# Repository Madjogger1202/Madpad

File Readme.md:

# Madpad

> Custom macropad based on **RP2040** with display, audio feedback, and per-key RGB lighting.  
> Designed as a versatile input device for PC with extra features for interaction and visualization.  

---

## What’s on the board
- **RP2040 microcontroller**  
  - USB device (HID, MIDI, or custom protocols)  
- **IPS display (0.96")**  
  - Controller: **ST7735**  
  - For status output, macro layers, menus, or visual effects  
- **Microphone**: INMP441ACEZ-R7 (I²S interface)  
- **Piezo buzzer** with transistor driver for sound feedback  
- **Rotary encoder** with integrated push button  
- **8 mechanical keys** (macro switches)  
- **RGB lighting**:  
  - 1× WS2812 (1×1 mm) LED per key  
  - Additional WS2812 LEDs distributed across the board for **ambient light effects**  

---

## Connectivity
- **USB Type-C** for both power and PC connection  
- Enumerates as **USB HID keyboard/macropad** (firmware-dependent)  
- Can be extended to **MIDI control surface** or custom USB interfaces  

---

## Use Cases
- Macro pad for productivity (shortcuts, hotkeys, macros)  
- Custom controller for audio/video editing software  
- Mini MIDI controller for music applications  
- Experiment platform for RGB effects + input devices  

---

## Notes
- LED layout allows both **per-key lighting** and **global light animations**.  
- Buzzer and microphone make the board suitable for **interactive feedback** or audio experiments.  
- Rotary encoder + display add flexibility for menus, layers, or volume control.  

---

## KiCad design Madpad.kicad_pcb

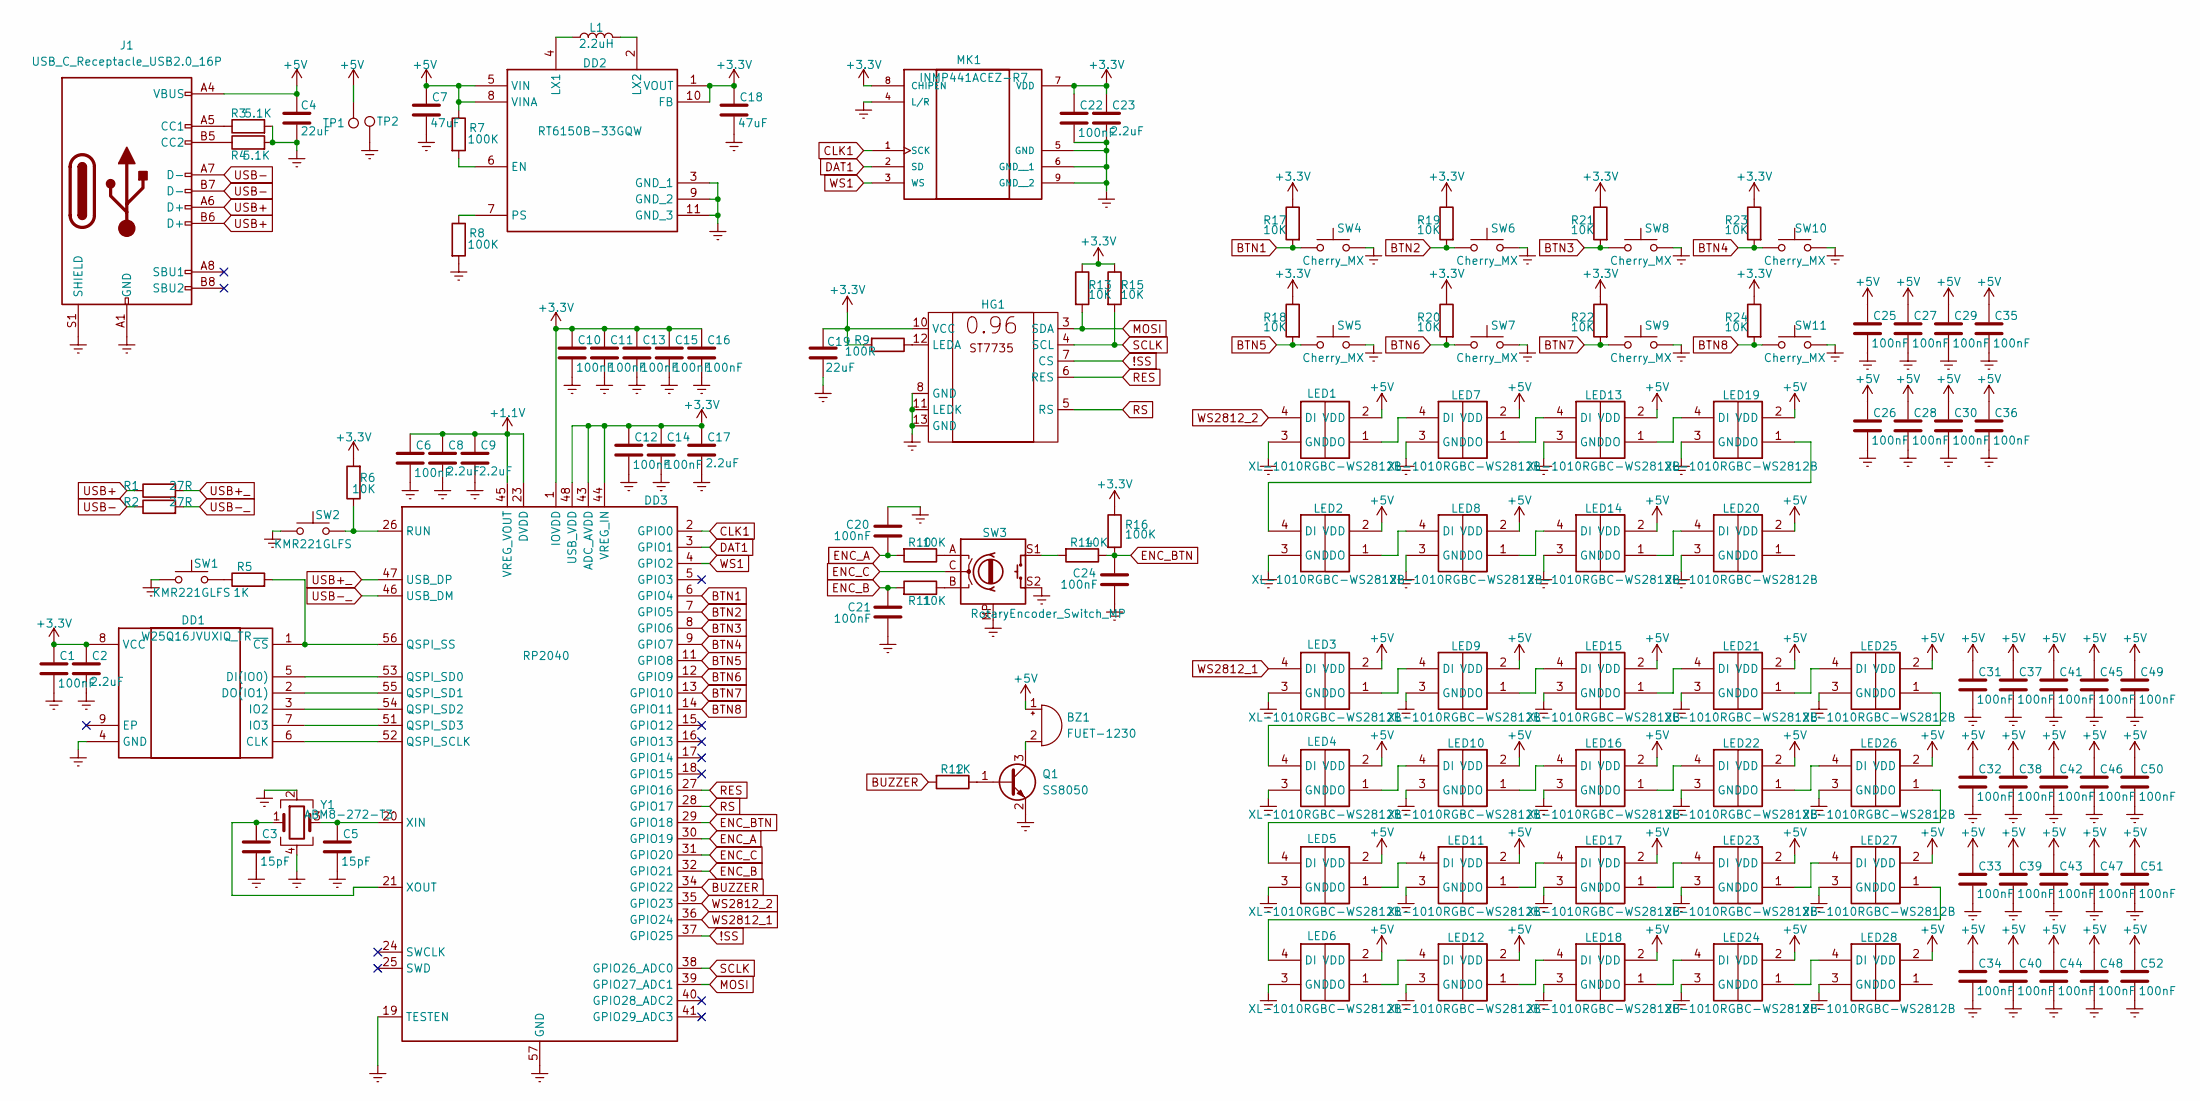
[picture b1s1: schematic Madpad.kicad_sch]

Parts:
BZ1: FUET-1230; Buzzer_Murata_PKLCS1212E
C1, C6, C10, C11, C12, C13, C14, C15, C16, C22: 100nF; C_0201_0603Metric
C2, C8, C9, C17, C23: 2.2uF; C_0402_1005Metric
C3, C5: 15pF; C_0201_0603Metric
C4, C19: 22uF; C_0402_1005Metric
C7, C18: 47uF; C_0805_2012Metric
C20, C21, C24, C25, C26, C27, C28, C29, C30, C31, C32, C33, C34, C35, C36, C37, C38, C39, C40, C41, C42, C43, C44, C45, C46, C47, C48, C49, C50, C51, C52: 100nF; C_0402_1005Metric
DD1: W25Q16JVUXIQ_TR; W25Q16JVUXIQ; Manufacturer_Part_Number W25Q16JVUXIQ TR; Mouser Part Number 454-W25Q16JVUXIQTR
DD2: RT6150B-33GQW; Manufacturer_Part_Number RT6150B-33GQW; Mouser Part Number 835-RT6150B-33GQW
DD3: RP2040; QFN-56-1EP_7x7mm_P0.4mm_EP3.2x3.2mm
HG1: ST7735 0.96
J1: USB_C_Receptacle_USB2.0_16P; USB_C_Receptacle_GCT_USB4105-xx-A_16P_TopMnt_Horizontal
L1: 2.2uH; L_1008_2520Metric
LED1, LED2, LED3, LED4, LED5, LED6, LED7, LED8, LED9, LED10, LED11, LED12, LED13, LED14, LED15, LED16, LED17, LED18, LED19, LED20, LED21, LED22, LED23, LED24, LED25, LED26, LED27, LED28: XL-1010RGBC-WS2812B; XL1010RGBCWS2812B; Manufacturer_Part_Number XL-1010RGBC-WS2812B
MK1: INMP441ACEZ-R7; INMP441; PARTREV 1.1
Q1: SS8050; SOT-23
R1, R2: 27R; R_0201_0603Metric
R3, R4: 5.1K; R_0402_1005Metric
R5, R12: 1K; R_0402_1005Metric
R6, R10, R11, R13, R14, R15, R17, R18, R19, R20, R21, R22, R23, R24: 10K; R_0402_1005Metric
R7, R8, R16: 100K; R_0402_1005Metric
R9: 100R; R_0402_1005Metric
SW1, SW2: KMR221GLFS; SW_SPST_PTS810
SW3: RotaryEncoder_Switch_MP; RotaryEncoder_Alps_EC11E-Switch_Vertical_H20mm
SW4, SW5, SW6, SW7, SW8, SW9, SW10, SW11: Cherry_MX; SW_Cherry_MX_PCB_1.00u
TP1, TP2: TestPoint_Pad_1.5x1.5mm
Y1: ABM8-272-T3; Crystal_SMD_3225-4Pin_3.2x2.5mm

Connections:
!SS: DD3.37 (GPIO25), HG1.7 (CS)
+1.1V: C6.1, C8.1, C9.1, DD3.23 (DVDD), DD3.45 (VREG_VOUT), DD3.50 (DVDD)
+3.3V: C1.1, C2.1, C10.1, C11.1, C12.1, C13.1, C14.1, C15.1, C16.1, C17.1, C18.1, C19.1, C22.1, C23.1, DD1.8 (VCC), DD2.1 (VOUT), DD2.10 (FB), DD3.1 (IOVDD), DD3.10 (IOVDD), DD3.22 (IOVDD), DD3.33 (IOVDD), DD3.42 (IOVDD), DD3.43 (ADC_AVDD), DD3.44 (VREG_IN), DD3.48 (USB_VDD), DD3.49 (IOVDD), HG1.10 (VCC), MK1.7 (VDD), MK1.8 (CHIPEN), R6.2, R9.2, R13.1, R15.1, R16.1, R17.1, R18.1, R19.1, R20.1, R21.1, R22.1, R23.1, R24.1
+5V: BZ1.1 (+), C4.1, C7.1, C25.1, C26.1, C27.1, C28.1, C29.1, C30.1, C31.1, C32.1, C33.1, C34.1, C35.1, C36.1, C37.1, C38.1, C39.1, C40.1, C41.1, C42.1, C43.1, C44.1, C45.1, C46.1, C47.1, C48.1, C49.1, C50.1, C51.1, C52.1, DD2.5 (VIN), DD2.8 (VINA), J1.A4 (VBUS), J1.A9 (VBUS), J1.B4 (VBUS), J1.B9 (VBUS), LED1.2 (VDD), LED2.2 (VDD), LED3.2 (VDD), LED4.2 (VDD), LED5.2 (VDD), LED6.2 (VDD), LED7.2 (VDD), LED8.2 (VDD), LED9.2 (VDD), LED10.2 (VDD), LED11.2 (VDD), LED12.2 (VDD), LED13.2 (VDD), LED14.2 (VDD), LED15.2 (VDD), LED16.2 (VDD), LED17.2 (VDD), LED18.2 (VDD), LED19.2 (VDD), LED20.2 (VDD), LED21.2 (VDD), LED22.2 (VDD), LED23.2 (VDD), LED24.2 (VDD), LED25.2 (VDD), LED26.2 (VDD), LED27.2 (VDD), LED28.2 (VDD), R7.1, TP1.1
BTN1: DD3.6 (GPIO4), R17.2, SW4.2
BTN2: DD3.7 (GPIO5), R19.2, SW6.2
BTN3: DD3.8 (GPIO6), R21.2, SW8.2
BTN4: DD3.9 (GPIO7), R23.2, SW10.2
BTN5: DD3.11 (GPIO8), R18.2, SW5.2
BTN6: DD3.12 (GPIO9), R20.2, SW7.2
BTN7: DD3.13 (GPIO10), R22.2, SW9.2
BTN8: DD3.14 (GPIO11), R24.2, SW11.2
BUZZER: DD3.34 (GPIO22), R12.2
CLK1: DD3.2 (GPIO0), MK1.1 (SCK)
DAT1: DD3.3 (GPIO1), MK1.2 (SD)
ENC_A: C20.2, DD3.30 (GPIO19), R10.2
ENC_B: C21.1, DD3.32 (GPIO21), R11.2
ENC_BTN: C24.1, DD3.29 (GPIO18), R14.1, R16.2
ENC_C: DD3.31 (GPIO20), SW3.C
Earth: C1.2, C2.2, C3.2, C4.2, C5.2, C6.2, C7.2, C8.2, C9.2, C10.2, C11.2, C12.2, C13.2, C14.2, C15.2, C16.2, C17.2, C18.2, C19.2, C20.1, C21.2, C22.2, C23.2, C24.2, C25.2, C26.2, C27.2, C28.2, C29.2, C30.2, C31.2, C32.2, C33.2, C34.2, C35.2, C36.2, C37.2, C38.2, C39.2, C40.2, C41.2, C42.2, C43.2, C44.2, C45.2, C46.2, C47.2, C48.2, C49.2, C50.2, C51.2, C52.2, DD1.4 (GND), DD2.3 (GND_1), DD2.9 (GND_2), DD2.11 (GND_3), DD3.19 (TESTEN), DD3.57 (GND), HG1.8 (GND), HG1.11 (LEDK), HG1.13 (GND), J1.A1 (GND), J1.A12 (GND), J1.B1 (GND), J1.B12 (GND), J1.S1 (SHIELD), LED1.3 (GND), LED2.3 (GND), LED3.3 (GND), LED4.3 (GND), LED5.3 (GND), LED6.3 (GND), LED7.3 (GND), LED8.3 (GND), LED9.3 (GND), LED10.3 (GND), LED11.3 (GND), LED12.3 (GND), LED13.3 (GND), LED14.3 (GND), LED15.3 (GND), LED16.3 (GND), LED17.3 (GND), LED18.3 (GND), LED19.3 (GND), LED20.3 (GND), LED21.3 (GND), LED22.3 (GND), LED23.3 (GND), LED24.3 (GND), LED25.3 (GND), LED26.3 (GND), LED27.3 (GND), LED28.3 (GND), MK1.4 (L/R), MK1.5 (GND), MK1.6 (GND__1), MK1.9 (GND__2), Q1.2 (E), R3.2, R4.2, R8.2, SW1.1, SW2.1, SW3.MP, SW3.S2, SW4.1, SW5.1, SW6.1, SW7.1, SW8.1, SW9.1, SW10.1, SW11.1, TP2.1, Y1.2, Y1.4
MOSI: DD3.39 (GPIO27_ADC1), HG1.3 (SDA), R13.2
unnamed: BZ1.2 (-), Q1.3 (C)
unnamed: DD1.6 (CLK), DD3.52 (QSPI_SCLK)
unnamed: DD1.5 (DI(IO0)), DD3.53 (QSPI_SD0)
unnamed: DD1.2 (DO(IO1)), DD3.55 (QSPI_SD1)
unnamed: DD1.3 (IO2), DD3.54 (QSPI_SD2)
unnamed: DD1.7 (IO3), DD3.51 (QSPI_SD3)
unnamed: DD1.1 (~CS), DD3.56 (QSPI_SS), R5.2
unnamed: DD2.6 (EN), R7.2
unnamed: DD2.4 (LX1), L1.1
unnamed: DD2.2 (LX2), L1.2
unnamed: DD2.7 (PS), R8.1
unnamed: DD3.26 (RUN), R6.1, SW2.2
unnamed: C5.1, DD3.20 (XIN), Y1.3
unnamed: C3.1, DD3.21 (XOUT), Y1.1
unnamed: HG1.12 (LEDA), R9.1
unnamed: J1.A5 (CC1), R3.1
unnamed: J1.B5 (CC2), R4.1
unnamed: LED1.1 (DO), LED7.4 (DI)
unnamed: LED2.1 (DO), LED8.4 (DI)
unnamed: LED3.1 (DO), LED9.4 (DI)
unnamed: LED4.1 (DO), LED10.4 (DI)
unnamed: LED10.1 (DO), LED16.4 (DI)
unnamed: LED5.1 (DO), LED11.4 (DI)
unnamed: LED11.1 (DO), LED17.4 (DI)
unnamed: LED6.1 (DO), LED12.4 (DI)
unnamed: LED12.1 (DO), LED18.4 (DI)
unnamed: LED7.1 (DO), LED13.4 (DI)
unnamed: LED13.1 (DO), LED19.4 (DI)
unnamed: LED8.1 (DO), LED14.4 (DI)
unnamed: LED14.1 (DO), LED20.4 (DI)
unnamed: LED9.1 (DO), LED15.4 (DI)
unnamed: LED15.1 (DO), LED21.4 (DI)
unnamed: LED16.1 (DO), LED22.4 (DI)
unnamed: LED17.1 (DO), LED23.4 (DI)
unnamed: LED18.1 (DO), LED24.4 (DI)
unnamed: LED2.4 (DI), LED19.1 (DO)
unnamed: LED21.1 (DO), LED25.4 (DI)
unnamed: LED22.1 (DO), LED26.4 (DI)
unnamed: LED23.1 (DO), LED27.4 (DI)
unnamed: LED24.1 (DO), LED28.4 (DI)
unnamed: LED4.4 (DI), LED25.1 (DO)
unnamed: LED5.4 (DI), LED26.1 (DO)
unnamed: LED6.4 (DI), LED27.1 (DO)
unnamed: Q1.1 (B), R12.1
unnamed: R5.1, SW1.2
unnamed: R10.1, SW3.A
unnamed: R11.1, SW3.B
unnamed: R14.2, SW3.S1
RES: DD3.27 (GPIO16), HG1.6 (RES)
RS: DD3.28 (GPIO17), HG1.5 (RS)
SCLK: DD3.38 (GPIO26_ADC0), HG1.4 (SCL), R15.2
USB+: J1.A6 (D+), J1.B6 (D+), R1.1
USB+_: DD3.47 (USB_DP), R1.2
USB-: J1.A7 (D-), J1.B7 (D-), R2.1
USB-_: DD3.46 (USB_DM), R2.2
WS1: DD3.4 (GPIO2), MK1.3 (WS)
WS2812_1: DD3.36 (GPIO24), LED3.4 (DI)
WS2812_2: DD3.35 (GPIO23), LED1.4 (DI)

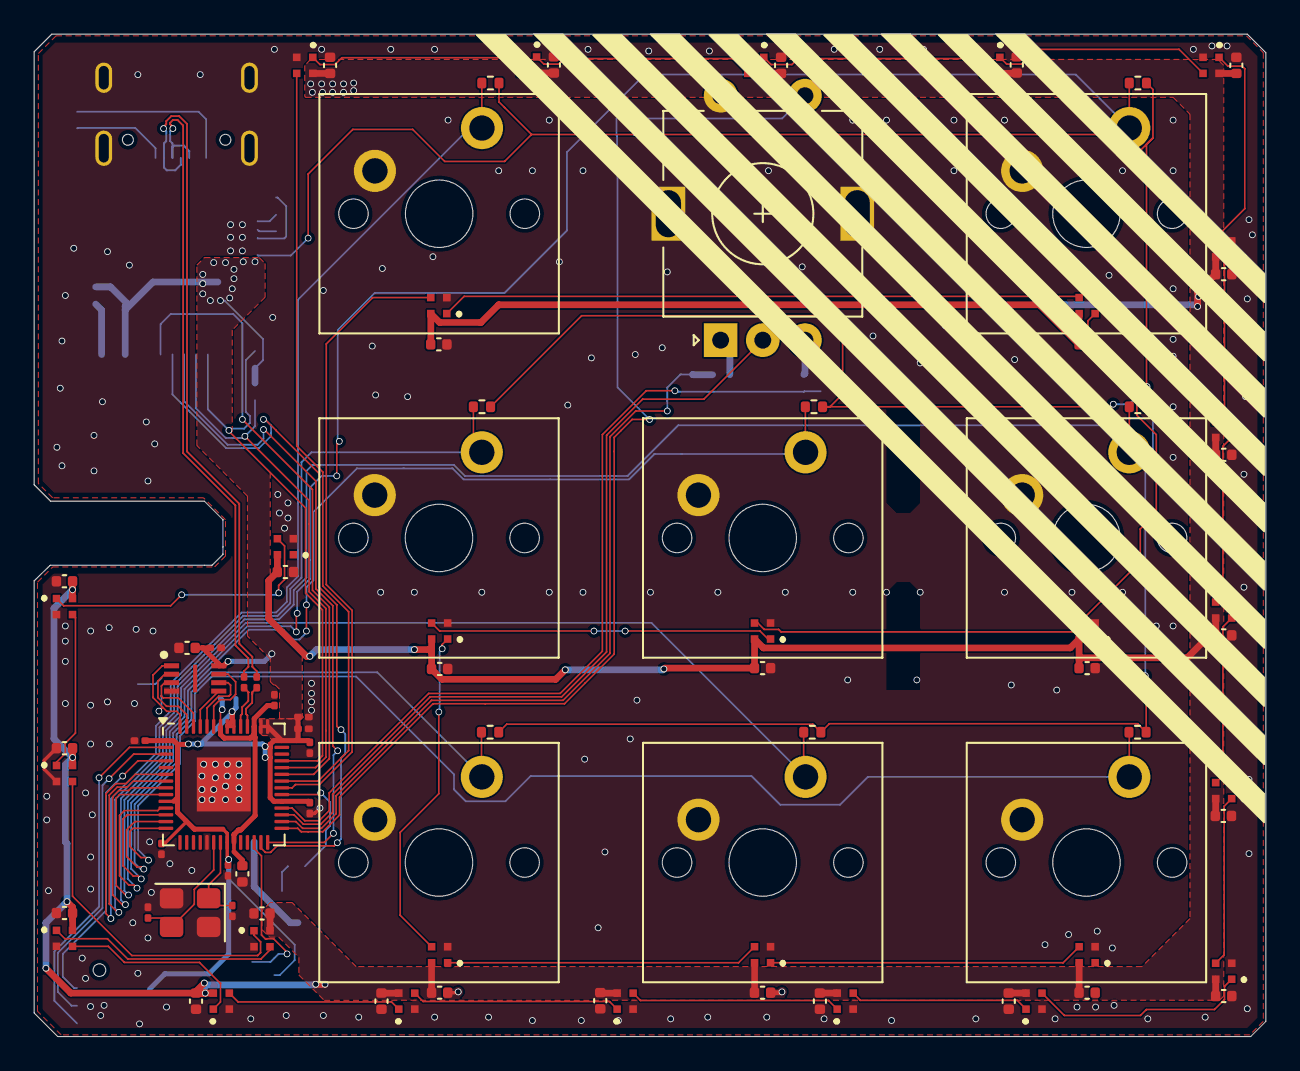
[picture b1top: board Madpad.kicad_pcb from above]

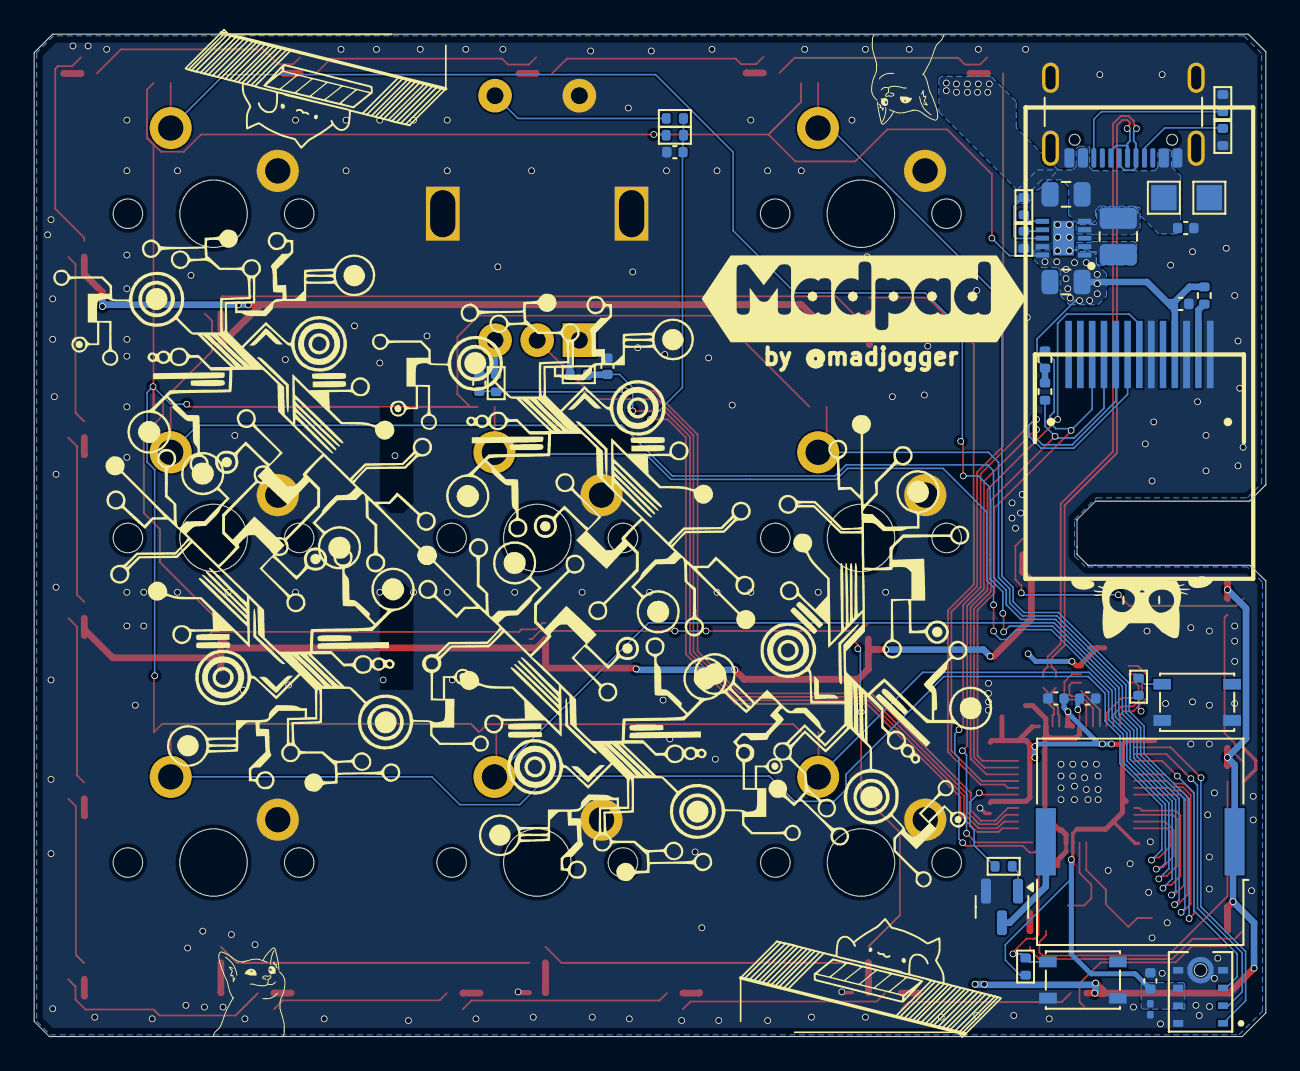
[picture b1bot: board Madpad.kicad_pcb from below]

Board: 2 copper layers, 73.0 x 59.4 mm, 128 parts (37 on the bottom side), 79 nets.

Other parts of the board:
kibuzzard-68CB22F7: G***; kibuzzard-68CB22F7

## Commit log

2025-09-17 rev0 ready
2025-09-17 Readme upd
